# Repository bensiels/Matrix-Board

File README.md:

# MatrixBoard
Matrix Board KiCad design

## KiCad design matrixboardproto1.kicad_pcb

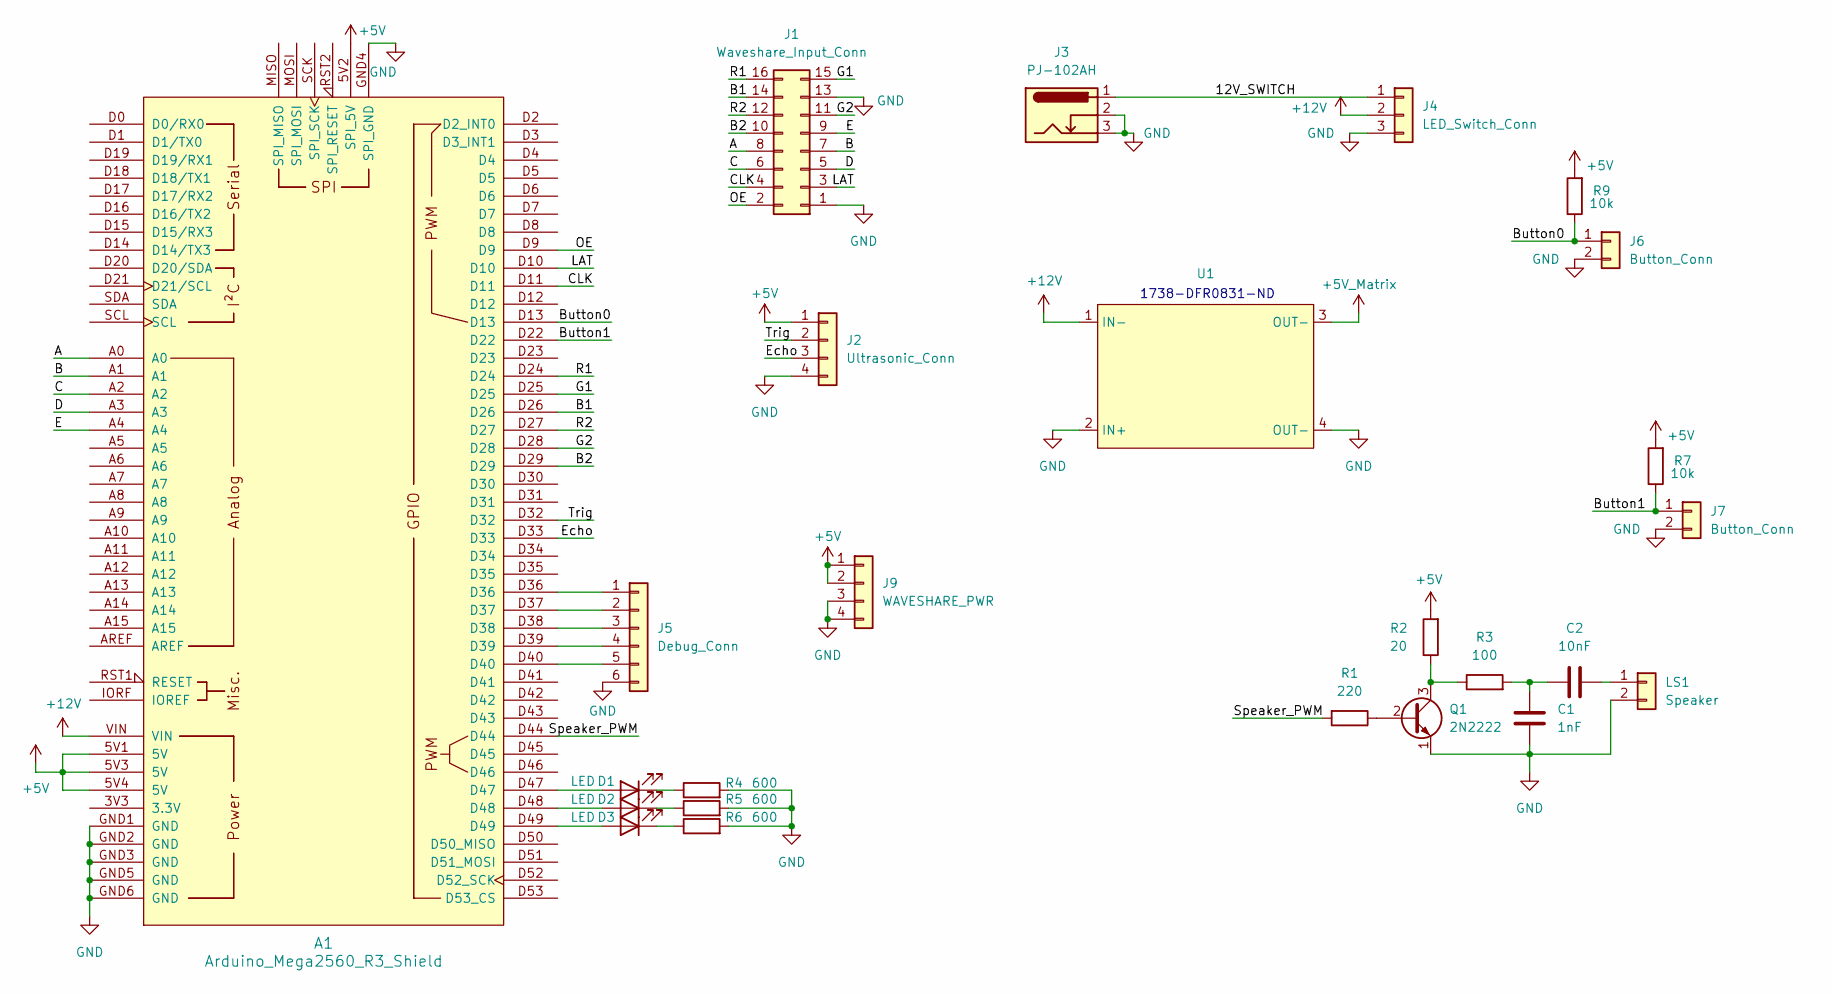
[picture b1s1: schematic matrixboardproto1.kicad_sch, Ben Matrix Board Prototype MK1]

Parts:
A1: Arduino_Mega2560_R3_Shield
C1: 1nF; C_0805_2012Metric_Pad1.18x1.45mm_HandSolder
C2: 10nF; C_0805_2012Metric_Pad1.18x1.45mm_HandSolder
D1, D2, D3: LED; LED_D5.0mm
J1: Waveshare_Input_Conn; IDC-Header_2x08_P2.54mm_Vertical
J2: Ultrasonic_Conn; PinHeader_1x04_P1.00mm_Vertical
J3: PJ-102AH; BarrelJack_GCT_DCJ200-10-A_Horizontal
J4: LED_Switch_Conn; FanPinHeader_1x03_P2.54mm_Vertical
J5: Debug_Conn; PinHeader_1x06_P1.00mm_Vertical
J6, J7: Button_Conn; PinHeader_1x02_P1.00mm_Vertical
J9: WAVESHARE_PWR; Molex_KK-396_5273-04A_1x04_P3.96mm_Vertical
LS1: Speaker; PinHeader_1x02_P1.00mm_Vertical
Q1: 2N2222; SOT-23_Handsoldering
R1: 220; R_0805_2012Metric_Pad1.20x1.40mm_HandSolder
R2: 20; R_0805_2012Metric_Pad1.20x1.40mm_HandSolder
R3: 100; R_0805_2012Metric_Pad1.20x1.40mm_HandSolder
R4, R5, R6: 600; R_0805_2012Metric_Pad1.20x1.40mm_HandSolder
R7, R9: 10k; R_0805_2012Metric_Pad1.20x1.40mm_HandSolder
U1: DFR_Regulator

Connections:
+12V: A1.VIN, J4.2, U1.1 (IN-)
/12V_SWITCH: J3.1, J4.1; also elsewhere on the board
/A: A1.A0, J1.8; also elsewhere on the board
/B: A1.A1, J1.7; also elsewhere on the board
/B1: A1.D26, J1.14; also elsewhere on the board
/B2: A1.D29, J1.10; also elsewhere on the board
/Button0: A1.D13, J6.1, R9.1
/Button1: A1.D22, J7.1, R7.1
/C: A1.A2, J1.6; also elsewhere on the board
/CLK: A1.D11, J1.4; also elsewhere on the board
/D: A1.A3, J1.5; also elsewhere on the board
/E: A1.A4, J1.9; also elsewhere on the board
/Echo: A1.D33, J2.3
/G1: A1.D25, J1.15; also elsewhere on the board
/G2: A1.D28, J1.11; also elsewhere on the board
/LAT: A1.D10, J1.3; also elsewhere on the board
/OE: A1.D9, J1.2; also elsewhere on the board
/R1: A1.D24, J1.16; also elsewhere on the board
/R2: A1.D27, J1.12; also elsewhere on the board
/Speaker_PWM: A1.D44, R1.2; also elsewhere on the board
/Trig: A1.D32, J2.2
GND: A1.GND1 (GND), A1.GND2 (GND), A1.GND3 (GND), A1.GND4 (SPI_GND), A1.GND5 (GND), A1.GND6 (GND), C1.1, J1.1, J1.13, J2.4, J3.2, J3.3, J4.3, J5.6, J6.2, J7.2, J9.3, J9.4, LS1.2, Q1.1 (E), R4.2, R5.2, R6.2, U1.2 (IN+), U1.4 (OUT-); also elsewhere on the board
unnamed: C1.2, C2.1, R3.2
unnamed 23: A1.D47, D1.2 (A); also elsewhere on the board
unnamed: D1.1 (K), R4.1
unnamed 25: A1.D48, D2.2 (A); also elsewhere on the board
unnamed: D2.1 (K), R5.1
unnamed 27: A1.D49, D3.2 (A); also elsewhere on the board
unnamed: D3.1 (K), R6.1
unnamed: A1.D36, J5.1
unnamed: A1.D37, J5.2
unnamed: A1.D38, J5.3
unnamed: A1.D39, J5.4
unnamed: A1.D40, J5.5
unnamed: C2.2, LS1.1
unnamed: Q1.2 (B), R1.1
unnamed: Q1.3 (C), R2.1, R3.1

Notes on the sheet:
1738-DFR0831-ND

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
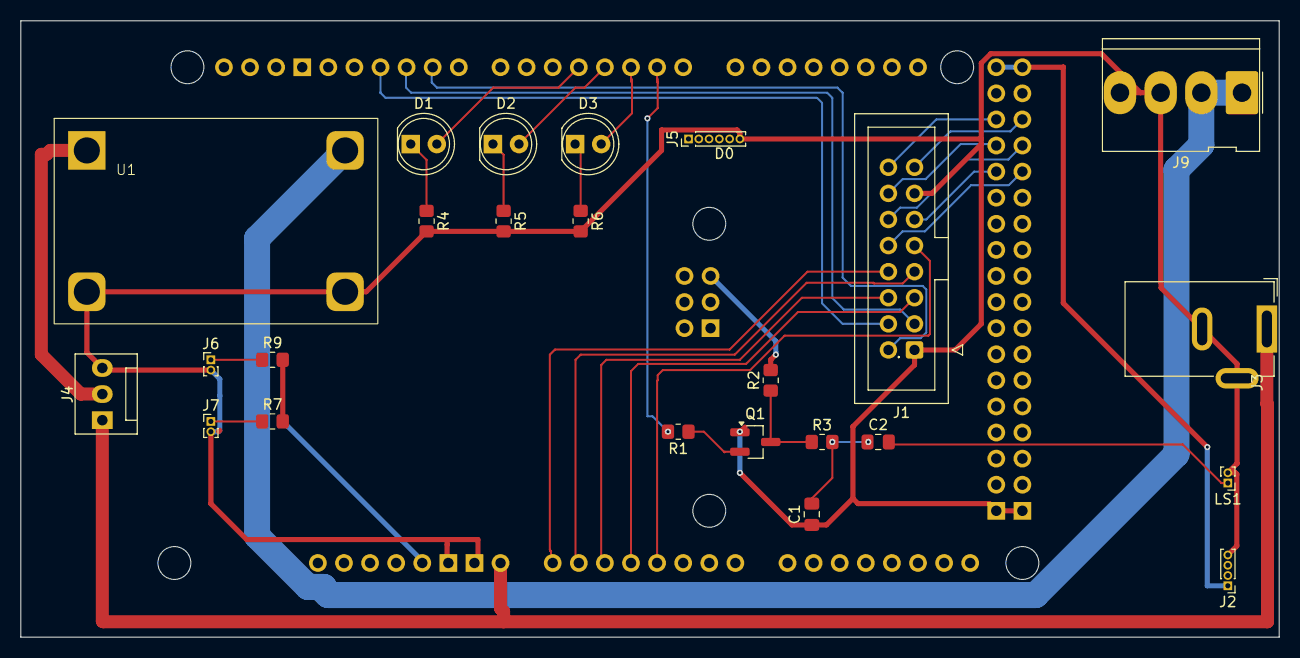
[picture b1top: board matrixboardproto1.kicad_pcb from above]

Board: 2 copper layers, 122.5 x 60.0 mm, 25 parts (0 on the bottom side), 32 nets.

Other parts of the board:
A**: Arduino_Mega2560_R3_Shield

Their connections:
/12V_SWITCH: A**.VIN; also elsewhere on the board
/A: A**.A0; also elsewhere on the board
/B: A**.A1; also elsewhere on the board
/B1: A**.D26; also elsewhere on the board
/B2: A**.D29; also elsewhere on the board
/C: A**.A2; also elsewhere on the board
/CLK: A**.D11; also elsewhere on the board
/D: A**.A3; also elsewhere on the board
/E: A**.A4; also elsewhere on the board
/G1: A**.D25; also elsewhere on the board
/G2: A**.D28; also elsewhere on the board
/LAT: A**.D10; also elsewhere on the board
/OE: A**.D9; also elsewhere on the board
/R1: A**.D24; also elsewhere on the board
/R2: A**.D27; also elsewhere on the board
/Speaker_PWM: A**.D1; also elsewhere on the board
GND: A**.GND2, A**.GND3, A**.GND5, A**.GND6; also elsewhere on the board
unnamed 23: A**.D4; also elsewhere on the board
unnamed 25: A**.D3; also elsewhere on the board
unnamed 27: A**.D2; also elsewhere on the board

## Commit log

2024-06-14 Added gitignore and readme
2024-06-14 Removed files that should be untracked
